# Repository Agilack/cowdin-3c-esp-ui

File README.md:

CowDIN ESP-UI
=============

This project is an electronic module to add a user interface (display +
buttons) as frontend of a DIN enclosure (3U). It can be used for example
with the cowdin ESP32 communication module (see cowdin-3b-esp32)

<table>
<tr>
<td></td>
<td></td>
</tr><tr>
<td>Fig1: Kicad 3D preview (top)</td>
<td>Fig2: Kicad 3D preview (bottom)</td>
</tr>
</table>

License
-------

This project is OpenHardware. Hardware design and materials are published
under terms of the Creative Commons ShareAlike license (CC-by-SA) see
hardware/License.md.

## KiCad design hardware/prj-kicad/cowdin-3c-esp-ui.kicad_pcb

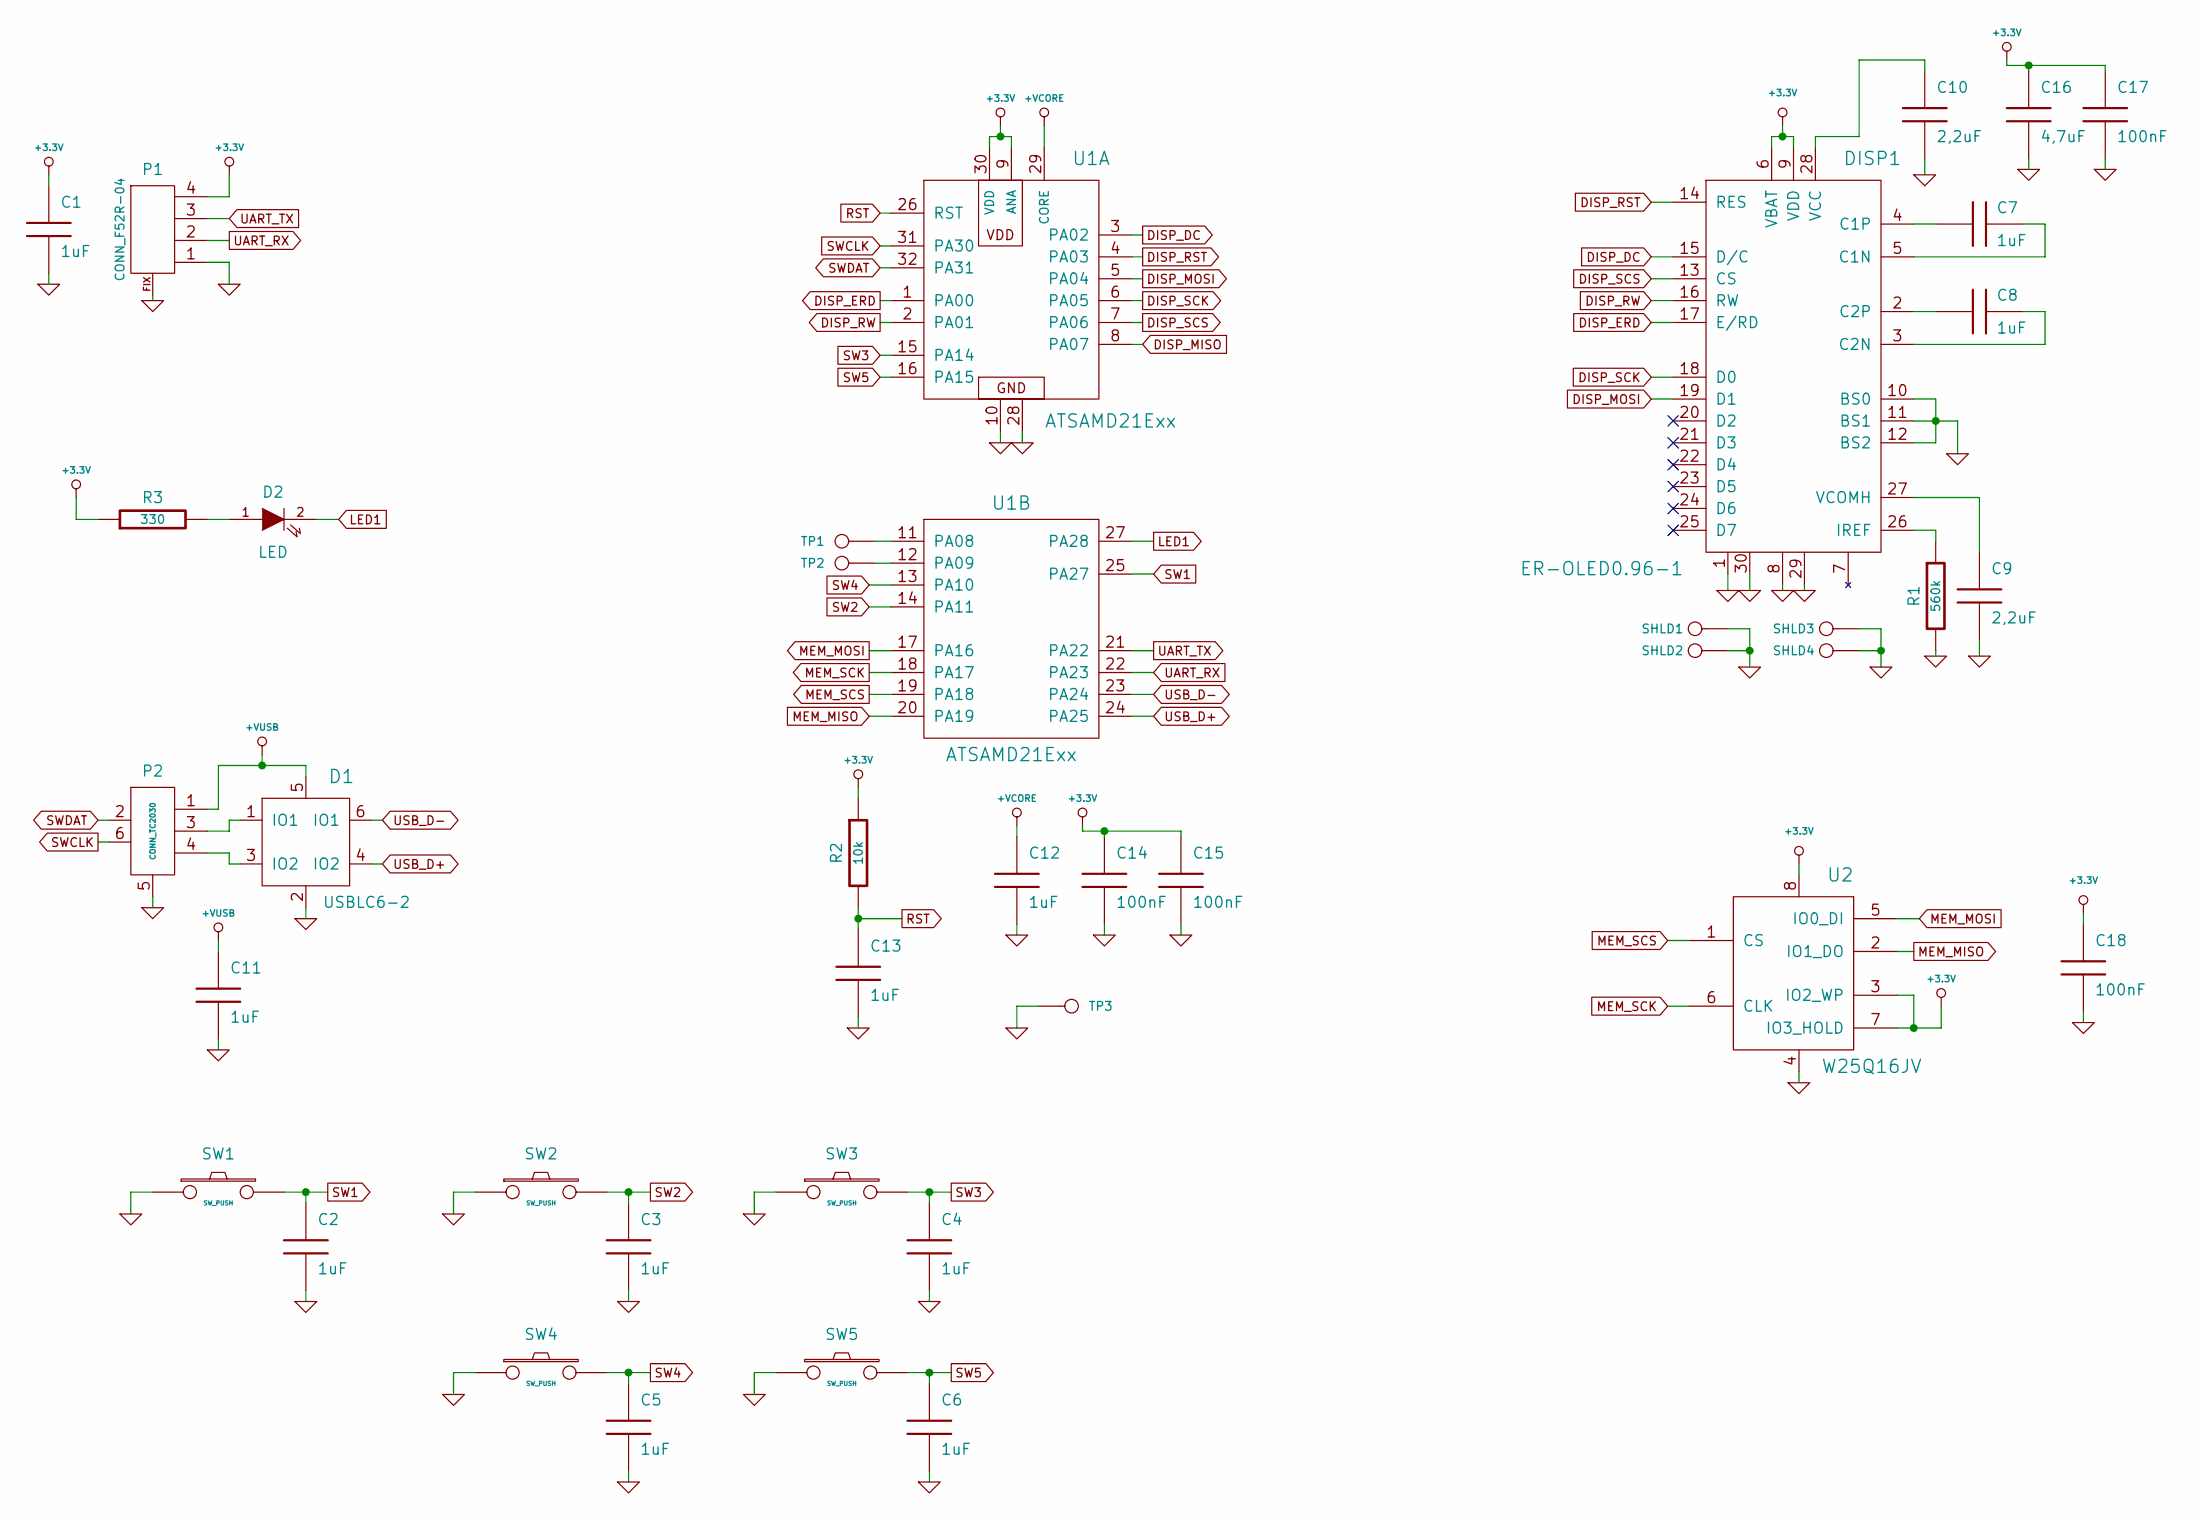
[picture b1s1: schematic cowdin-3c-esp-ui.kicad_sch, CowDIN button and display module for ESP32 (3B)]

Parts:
C1, C2, C3, C4, C5, C6, C7, C8, C11, C12, C13: 1uF; SMD0603
C9, C10: 2,2uF; SMD0603
C14, C15, C17, C18: 100nF; SMD0603
C16: 4,7uF; SMD0805
D1: USBLC6-2; SOT23-6
D2: LED; SMD0805
DISP1: ER-OLED0.96-1; DISP_EROL30
P1: CONN_F52R-04
P2: CONN_TC2030; TC2030-MCP-FP
R1: 560k; SMD0603
R2: 10k; SMD0603
R3: 330; SMD0603
SHLD1, SHLD2, SHLD3, SHLD4: CONN_1; SHLD_PAD
SW1, SW2, SW3, SW4, SW5: SW_PUSH; SW_TSC015xx
TP1, TP2, TP3: CONN_1; TP_SMD
U1: ATSAMD21Exx; TQFP32
U2: W25Q16JV; SOIC-8

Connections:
+3.3V: C1.1, C14.1, C15.1, C16.1, C17.1, C18.1, DISP1.6 (VBAT), DISP1.9 (VDD), P1.4, R2.1, R3.1, U1.9 (ANA), U1.30 (VDD), U2.3 (IO2_WP), U2.7 (IO3_HOLD), U2.8
+VCORE: C12.1, U1.29 (CORE)
+VUSB: C11.1, D1.5, P2.1 (PWR)
DISP_DC: DISP1.15 (D/C), U1.3 (PA02)
DISP_ERD: DISP1.17 (E/RD), U1.1 (PA00)
DISP_MISO: U1.8 (PA07)
DISP_MOSI: DISP1.19 (D1), U1.5 (PA04)
DISP_RST: DISP1.14 (RES), U1.4 (PA03)
DISP_RW: DISP1.16 (RW), U1.2 (PA01)
DISP_SCK: DISP1.18 (D0), U1.6 (PA05)
DISP_SCS: DISP1.13 (CS), U1.7 (PA06)
LED1: D2.2 (K), U1.27 (PA28)
MEM_MISO: U1.20 (PA19), U2.2 (IO1_DO)
MEM_MOSI: U1.17 (PA16), U2.5 (IO0_DI)
MEM_SCK: U1.18 (PA17), U2.6 (CLK)
MEM_SCS: U1.19 (PA18), U2.1 (CS)
unnamed: C7.1, DISP1.4 (C1P)
unnamed: C7.2, DISP1.5 (C1N)
unnamed: C8.1, DISP1.2 (C2P)
unnamed: C8.2, DISP1.3 (C2N)
unnamed: C9.1, DISP1.27 (VCOMH)
unnamed: C10.1, DISP1.28 (VCC)
unnamed: D1.1 (IO1), P2.3 (USB1)
unnamed: D1.3 (IO2), P2.4 (USB2)
unnamed: D2.1 (A), R3.2
unnamed: DISP1.26 (IREF), R1.1
unnamed: TP1.1, U1.11 (PA08)
unnamed: TP2.1, U1.12 (PA09)
RST: C13.1, R2.2, U1.26 (RST)
SW1: C2.1, SW1.2, U1.25 (PA27)
SW2: C3.1, SW2.2, U1.14 (PA11)
SW3: C4.1, SW3.2, U1.15 (PA14)
SW4: C5.1, SW4.2, U1.13 (PA10)
SW5: C6.1, SW5.2, U1.16 (PA15)
SWCLK: P2.6 (DBG2), U1.31 (PA30)
SWDAT: P2.2 (DBG1), U1.32 (PA31)
UART_RX: P1.2 (PM), U1.22 (PA23)
UART_TX: P1.3, U1.21 (PA22)
USB_D+: D1.4 (IO2), U1.24 (PA25)
USB_D-: D1.6 (IO1), U1.23 (PA24)

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
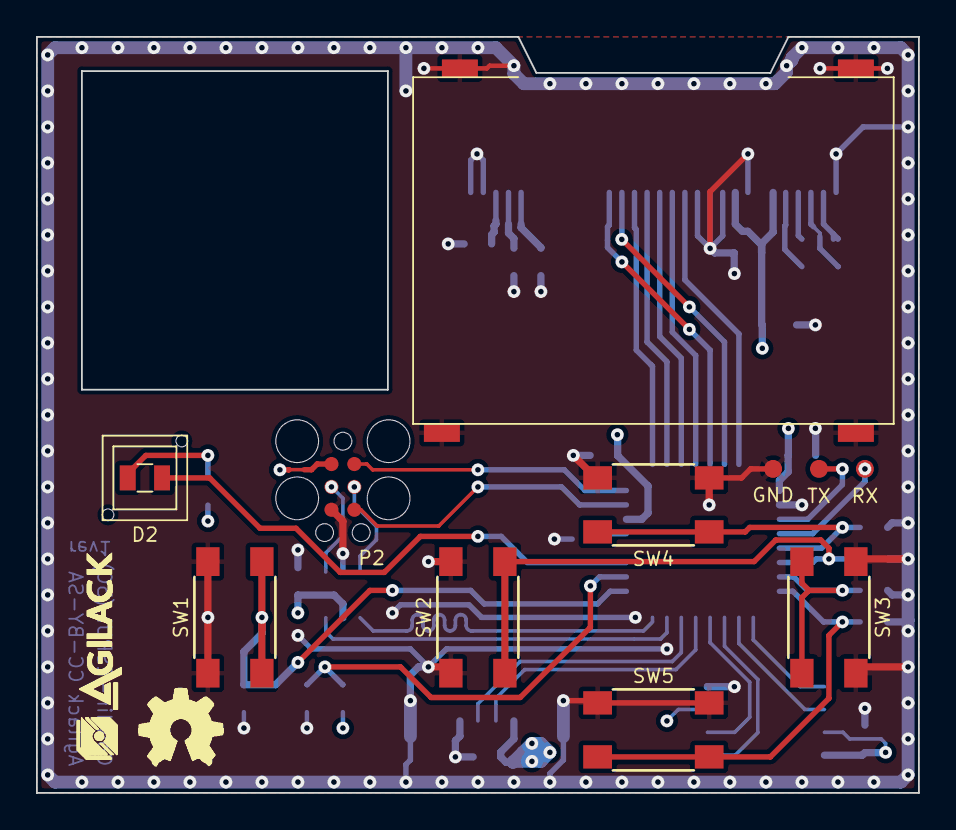
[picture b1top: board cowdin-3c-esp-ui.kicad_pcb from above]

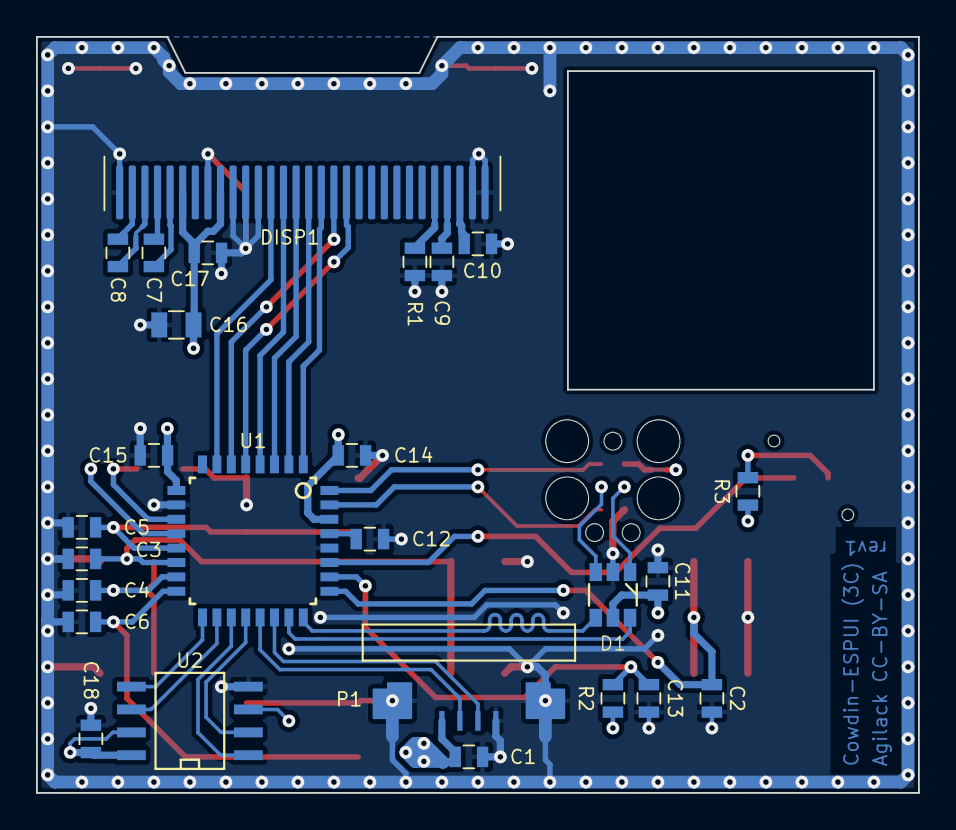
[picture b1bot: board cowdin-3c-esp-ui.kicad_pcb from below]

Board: 4 copper layers, 49.0 x 42.0 mm, 42 parts (26 on the bottom side), 40 nets.

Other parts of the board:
agilack-11.5: 450px; logo-agilack-11.5
ohw_logo: VAL**; logo-ohw

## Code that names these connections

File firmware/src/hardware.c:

/**
 * @file  hardware.c
 * @brief Low-level hardware configuration
 *
 * @author Saint-Genest Gwenael <gwen@cowlab.fr>
 * @copyright Agilack (c) 2022
 *
 * @page License
 * Cowdin-3C-ui firmware is free software: you can redistribute it and/or
 * modify it under the terms of the GNU Lesser General Public License
 * version 3 as published by the Free Software Foundation. You should
 * have received a copy of the GNU Lesser General Public License along
 * with this program, see LICENSE.md file for more details.
 * This program is distributed WITHOUT ANY WARRANTY.
 */
#include "hardware.h"

static inline void hw_init_button(void);
static inline void hw_init_clock(void);
static inline void hw_init_display(void);
static inline void hw_init_leds(void);
static inline void hw_init_uart(void);

/**
 * @brief Called on startup to init processor, clocks and some peripherals
 *
 */
void hw_init(void)
{
	/* Use PM to configure clock sources */
	reg8_wr(PM_ADDR + 0x08, 0x00); /* CPU  clock select (CPUSEL)  */
	reg8_wr(PM_ADDR + 0x09, 0x00); /* APBA clock select (APBASEL) */
	reg8_wr(PM_ADDR + 0x0A, 0x00); /* APBB clock select (APBBSEL) */
	reg8_wr(PM_ADDR + 0x0B, 0x00); /* APBC clock select (APBCSEL) */

	hw_init_clock();

	hw_init_button();
	hw_init_display();
	hw_init_leds();
	hw_init_uart();
}

/**
 * @brief Initialize io for pushbutton
 *
 */
static inline void hw_init_button(void)
{
	/* Configure SW1 (PA27) */
	reg_wr (0x60000000 + 0x04, (1 << 27)); // DIR
	reg_wr (0x60000000 + 0x18, (1 << 27)); // Set out=1 for pull-up
	reg8_wr(0x60000000 + 0x5B,  0x06);     // PINCFG: Input with pull-up
	reg_set(0x60000000 + 0x24, (1 << 27)); // Continuous sampling

	/* Configure SW2 (PA11) */
	reg_wr (0x60000000 + 0x04, (1 << 11)); // DIR
	reg_wr (0x60000000 + 0x18, (1 << 11)); // Set out=1 for pull-up
	reg8_wr(0x60000000 + 0x4B,  0x06);     // PINCFG: Input with pull-up
	reg_set(0x60000000 + 0x24, (1 << 11)); // Continuous sampling

	/* Configure SW3 (PA14) */
	reg_wr (0x60000000 + 0x04, (1 << 14)); // DIR
	reg_wr (0x60000000 + 0x18, (1 << 14)); // Set out=1 for pull-up
	reg8_wr(0x60000000 + 0x4E,  0x06);     // PINCFG: Input with pull-up
	reg_set(0x60000000 + 0x24, (1 << 14)); // Continuous sampling

	/* Configure SW4 (PA10) */
	reg_wr (0x60000000 + 0x04, (1 << 10)); // DIR
	reg_wr (0x60000000 + 0x18, (1 << 10)); // Set out=1 for pull-up
	reg8_wr(0x60000000 + 0x4A,  0x06);     // PINCFG: Input with pull-up
	reg_set(0x60000000 + 0x24, (1 << 10)); // Continuous sampling

	/* Configure SW5 (PA15) */
	reg_wr (0x60000000 + 0x04, (1 << 15)); // DIR
	reg_wr (0x60000000 + 0x18, (1 << 15)); // Set out=1 for pull-up
	reg8_wr(0x60000000 + 0x4F,  0x06);     // PINCFG: Input with pull-up
	reg_set(0x60000000 + 0x24, (1 << 15)); // Continuous sampling
}

/**
 * @brief Configure oscillators and Generic Clock Controller (GCLK)
 *
 */
static inline void hw_init_clock(void)
{
	u32 dfll_coarse, dfll_cfg;
	u32 v;

	/* Configure internal 8MHz oscillator */
	v = reg_rd(SYSCTRL_ADDR + 0x20); /* Read OSC8M config register */
	v &= 0xFFFFFC3F;                 /* Clear prescaler and OnDemand flag */
	reg_wr(SYSCTRL_ADDR + 0x20, v);  /* Write-back OSC8M */
	/* Wait for internal 8MHz oscillator stable and ready */
	while( ! (reg_rd(SYSCTRL_ADDR + 0x0C) & 0x08))
		;

	/* Activate the internal 32kHz oscillator */
	v  = (((reg_rd(0x00806024) >> 6) & 0x7F) << 16); /* Calib bits 38:44 */
	v |= (1 << 1); /* Set enable bit */
	v |= (1 << 2); /* Output Enable */
	reg_wr(SYSCTRL_ADDR + 0x18, v);
	/* Wait for internal 32kHz oscillator stable and ready */
	while( ! (reg_rd(SYSCTRL_ADDR + 0x0C) & 0x04))
		;

	/* Set Divisor for GCLK0 : enabled, OSC8M, no divisor */
	reg_wr(GCLK_ADDR + 0x08, (1 << 8) | 0x00);
	reg_wr(GCLK_ADDR + 0x04, (1 << 16) | (0x06 << 8) | 0x00);
	/* Set Divisor for GCLK1 : enabled, OSC8M, no divisor */
	reg_wr(GCLK_ADDR + 0x08, (1 << 8) | 0x01);
	reg_wr(GCLK_ADDR + 0x04, (1 << 16) | (0x06 << 8) | 0x01);
	/* Set Divisor for GCLK2 : disabled */
	reg_wr(GCLK_ADDR + 0x08, (1 << 8) | 0x02);
	reg_wr(GCLK_ADDR + 0x04, (0 << 16) | (0x06 << 8) | 0x02);
	/* Set Divisor for GCLK3 : disabled */
	reg_wr(GCLK_ADDR + 0x08, (1 << 8) | 0x03);
	reg_wr(GCLK_ADDR + 0x04, (0 << 16) | (0x06 << 8) | 0x03);
	/* Set Divisor for GCLK4 : disabled */
	reg_wr(GCLK_ADDR + 0x08, (1 << 8) | 0x04);
	reg_wr(GCLK_ADDR + 0x04, (0 << 16) | (0x06 << 8) | 0x04);
	/* Set Divisor for GCLK5 : enabled, OSC32k, no divisor */
	reg_wr(GCLK_ADDR + 0x08, (1 << 8) | 0x05);
	reg_wr(GCLK_ADDR + 0x04, (1 << 16) | (0x04 << 8) | 0x05);
	/* Set Divisor for GCLK6 : disabled */
	reg_wr(GCLK_ADDR + 0x08, (1 << 8) | 0x06);
	reg_wr(GCLK_ADDR + 0x04, (0 << 16) | (0x06 << 8) | 0x06);
	/* Set Divisor for GCLK7 : enabled, DFLL48M, no divisor */
	reg_wr(GCLK_ADDR + 0x08, (1 << 8) | 0x07);
	reg_wr(GCLK_ADDR + 0x04, (1 << 16) | (0x07 << 8) | 0x07);
	/* Set Divisor for GCLK8 : disabled */
	reg_wr(GCLK_ADDR + 0x08, (1 << 8) | 0x08);
	reg_wr(GCLK_ADDR + 0x04, (0 << 16) | (0x06 << 8) | 0x08);

	/* Enable DFLL block */
	reg16_wr(SYSCTRL_ADDR + 0x24, (1 << 1));
	while ( ! (reg_rd(SYSCTRL_ADDR + 0x0C) & 0x00000010))
		;
	/* Configure DFLL multiplier (DFLLMUL) */
	reg_wr(SYSCTRL_ADDR + 0x2c, (1 << 20) | (1 << 16) | 0xBB80);
	/* Set DFLL coarse calibration value */
	dfll_coarse = (*(u32 *)0x00806024 >> 26) & 0x3F;
	reg_wr(SYSCTRL_ADDR + 0x28, (0x0000 << 16) | (dfll_coarse << 10) | 512);
	/* Configure DFLL */
	dfll_cfg = (1 << 10)  /* Bypass Coarse Lock      */
	         | (1 <<  9)  /* Quick Lock Disable      */
	         | (1 <<  5)  /* USB Clock Recovery Mode */
	         | (1 <<  2)  /* Mode: closed-loop       */
	         | (1 <<  1); /* Enable DFLL             */
	reg16_wr(SYSCTRL_ADDR + 0x24, dfll_cfg);
	/* Wait depending on DFLL mode (closed or open loop) */
	if (reg_rd(SYSCTRL_ADDR + 0x24) & 0x04)
	{
		u32 wait_mask = 0x10;
		/* Wait for DFLL to be ready */
		while((reg_rd(SYSCTRL_ADDR + 0X0C) & wait_mask) != wait_mask)
			;
	}
	else
	{
		/* Wait for DFLL to be ready */
		while((reg_rd(SYSCTRL_ADDR + 0X0C) & 0x10) == 0)
			;
	}
	/* Wait end of clock domains synchronization */
	while (reg8_rd(GCLK_ADDR + 0x01) & 0x80)
		;

	/* Update NVM (flash memory wait-state before switching to 48MHz) */
	reg_wr(NVM_ADDR + 0x04, (1 << 1)); /* 1 wait state (see table 37-40) */

	/* Set Divisor for GCLK0 : enabled, DFLL48M, no divisor */
	reg_wr(GCLK_ADDR + 0x08, (1 << 8) | 0x00);
	reg_wr(GCLK_ADDR + 0x04, (1 << 16) | (0x07 << 8) | 0x00);
}

/**
 * @brief Initialize IOs used to control display
 *
 */
static inline void hw_init_display(void)
{
	/* Configure DISP_RST (PA03) */
	reg_wr(0x60000000 + 0x14, (1 << 03)); // OUT=0 (active reset !)
	reg_wr(0x60000000 + 0x08, (1 << 03)); // DIR: output
	reg8_wr(0x60000000 + 0x43, 0x00); // PINCFG: normal, no-pull, no pmux

	/* Configure DISP_DC (PA02) */
	reg_wr(0x60000000 + 0x14, (1 << 02)); // OUT=0
	reg_wr(0x60000000 + 0x08, (1 << 02)); // DIR: output
	reg8_wr(0x60000000 + 0x42, 0x00); // PINCFG: normal, no-pull, no pmux

	/* Configure DISP_RW (PA01) */
	reg_wr(0x60000000 + 0x14, (1 << 01)); // OUT=0
	reg_wr(0x60000000 + 0x08, (1 << 01)); // DIR: output
	reg8_wr(0x60000000 + 0x41, 0x00); // PINCFG: normal, no-pull, no pmux

	/* Configure DISP_ERD (PA00) */
	reg_wr(0x60000000 + 0x14, (1 << 00)); // OUT=0
	reg_wr(0x60000000 + 0x08, (1 << 00)); // DIR: output
	reg8_wr(0x60000000 + 0x40, 0x00); // PINCFG: normal, no-pull, no pmux

	/* Configure DISP_NSS (PA06) */
	reg_wr(0x60000000 + 0x18, (1 << 06)); // OUT=1
	reg_wr(0x60000000 + 0x08, (1 << 06)); // DIR: output
	reg8_wr(0x60000000 + 0x46, 0x00); // PINCFG: normal, no-pull, no pmux

	/* Configure SPI lines (PA04, PA05, PA06, PA07) */
	reg8_wr(0x60000000 + 0x44, 0x01); // PINCFG: Set PMUX for PA04 (MOSI)
	reg8_wr(0x60000000 + 0x45, 0x01); // PINCFG: Set PMUX for PA05 (SCK)
	reg8_wr(0x60000000 + 0x46, 0x00); // PINCFG: No-PMUX  for PA06 (NSS)
	reg8_wr(0x60000000 + 0x47, 0x01); // PINCFG: Set PMUX for PA07 (MISO)
	reg8_wr(0x60000000 + 0x32, (0x03 << 4) | (0x03 << 0)); // PMUX: D
	reg8_wr(0x60000000 + 0x33, (0x03 << 4) | (0x03 << 0)); // PMUX: D
}

/**
 * @brief Initialize the LED io
 *
 */
static inline void hw_init_leds(void)
{
	/* Set LED "OFF" (pin output=1) */
	reg_wr(0x60000000 + 0x18, (1 << 28));
	/* DIR: Set PA28 as output */
	reg_wr(0x60000000 + 0x08, (1 << 28));
	/* PINCFG: Configure PA28 (strong strength, no pull, no pmux) */
	reg8_wr(0x60000000 + 0x5C, 0x40);
}

/**
 * @brief Initialize UART ios
 *
 */
static inline void hw_init_uart(void)
{
	/* Configure main UART (SERCOM3) */
	reg8_wr(0x60000000 + 0x56, 0x01);    // PINCFG: Set PMUX for PA22 (TX)
	reg8_wr(0x60000000 + 0x57, 0x01);    // PINCFG: Set PMUX for PA23 (RX)
	reg8_wr(0x60000000 + 0x3B, (0x02 << 4) | (0x02 << 0)); // PMUX: C

	/* Configure console/debug port (SERCOM2) */
	reg8_wr(0x60000000 + 0x48, 0x01);    // PINCFG: Set PMUX for PA08 (TX)
	reg8_wr(0x60000000 + 0x49, 0x01);    // PINCFG: Set PMUX for PA09 (RX)
	reg8_wr(0x60000000 + 0x34, (0x03 << 4) | (0x03 << 0)); // PMUX: D
}
/* EOF */

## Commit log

2022-06-10 Hardware: Create pcb skeleton, add display and buttons
2022-06-11 Hardware: Add MCU and main components. Create productions files for rev1
2022-06-17 Firmware: Create basic firmware (configure IOs, control LED and UART)
2022-06-18 Firmware: Add driver for OLED display (spi) and remap uart to avoid conflict

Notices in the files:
hardware/prj-kicad/cowdin-3c-esp-ui.kicad_pcb:
Agilack CC-BY-SA
